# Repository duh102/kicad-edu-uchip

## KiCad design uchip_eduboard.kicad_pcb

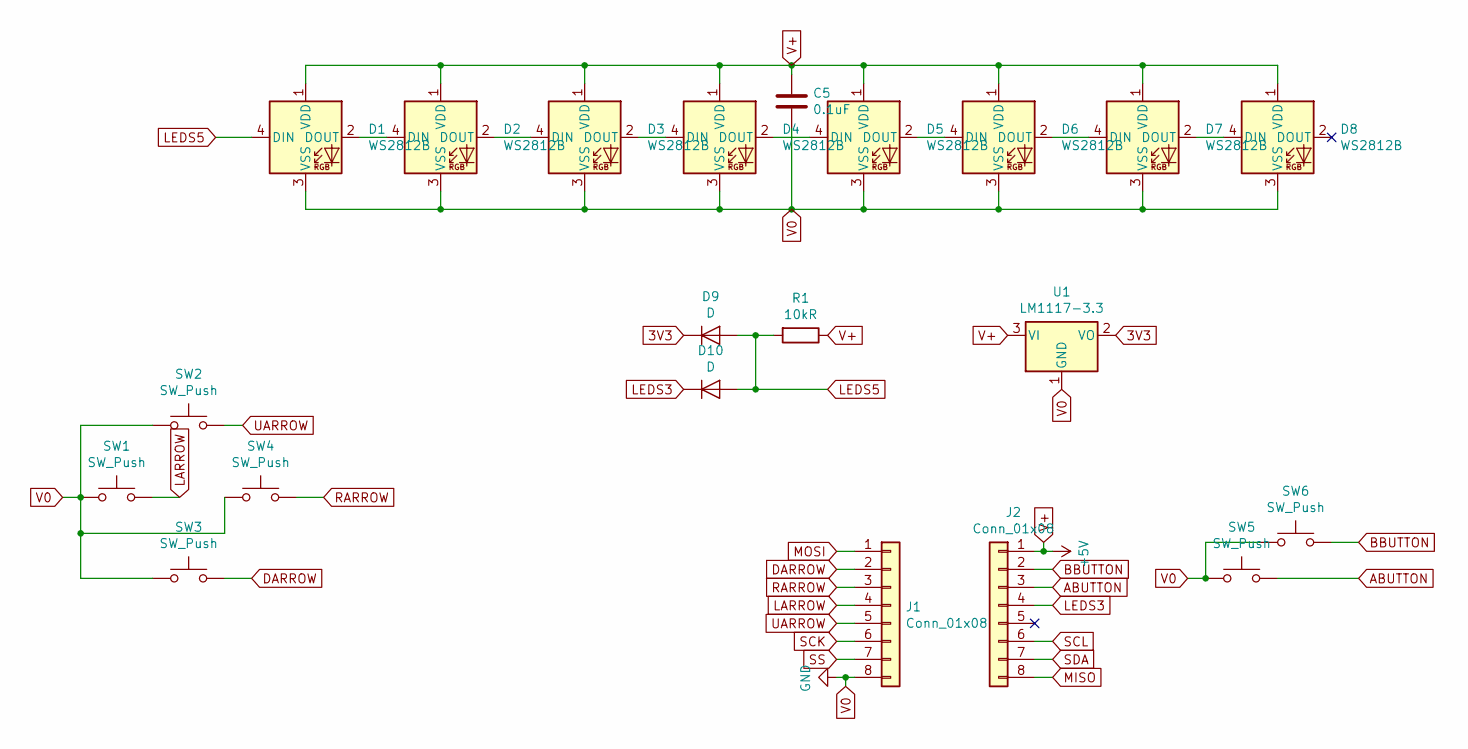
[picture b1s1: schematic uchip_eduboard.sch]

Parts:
C5: 0.1uF; C_0603_1608Metric
D1, D2, D3, D4, D5, D6, D7, D8: WS2812B; LED_WS2812B_PLCC4_5.0x5.0mm_P3.2mm
D9, D10: D; D_SOD-323F
J1, J2: Conn_01x08; PinSocket_1x08_P2.54mm_Vertical
R1: 10kR; R_0603_1608Metric
SW1, SW2, SW3, SW4, SW5, SW6: SW_Push; SW_SPST_TL3342
U1: LM1117-3.3; SOT-89-3

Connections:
3V3: D9.1 (K), U1.2 (VO)
ABUTTON: J2.3, SW5.2
BBUTTON: J2.2, SW6.2
DARROW: J1.2, SW3.2
LARROW: J1.4, SW1.2
LEDS3: D10.1 (K), J2.4
LEDS5: D1.4 (DIN), D9.2 (A), D10.2 (A), R1.2
MISO: J2.8
MOSI: J1.1
unnamed: D1.2 (DOUT), D2.4 (DIN)
unnamed: D2.2 (DOUT), D3.4 (DIN)
unnamed: D3.2 (DOUT), D4.4 (DIN)
unnamed: D4.2 (DOUT), D5.4 (DIN)
unnamed: D5.2 (DOUT), D6.4 (DIN)
unnamed: D6.2 (DOUT), D7.4 (DIN)
unnamed: D7.2 (DOUT), D8.4 (DIN)
RARROW: J1.3, SW4.2
SCK: J1.6
SCL: J2.6
SDA: J2.7
SS: J1.7
UARROW: J1.5, SW2.2
V0: C5.2, D1.3 (VSS), D2.3 (VSS), D3.3 (VSS), D4.3 (VSS), D5.3 (VSS), D6.3 (VSS), D7.3 (VSS), D8.3 (VSS), J1.8, SW1.1, SW2.1, SW3.1, SW4.1, SW5.1, SW6.1, U1.1 (GND)
V+: C5.1, D1.1 (VDD), D2.1 (VDD), D3.1 (VDD), D4.1 (VDD), D5.1 (VDD), D6.1 (VDD), D7.1 (VDD), D8.1 (VDD), J2.1, R1.1, U1.3 (VI)

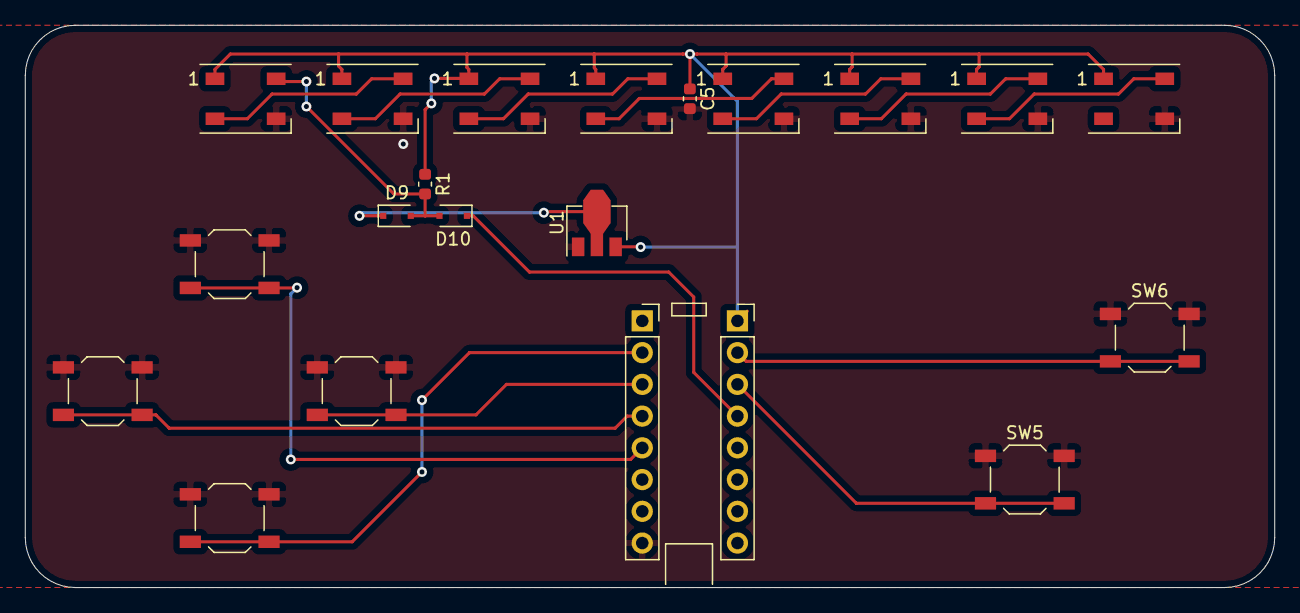
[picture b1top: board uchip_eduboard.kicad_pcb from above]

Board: 2 copper layers, 100.0 x 45.0 mm, 21 parts (0 on the bottom side), 18 nets.
